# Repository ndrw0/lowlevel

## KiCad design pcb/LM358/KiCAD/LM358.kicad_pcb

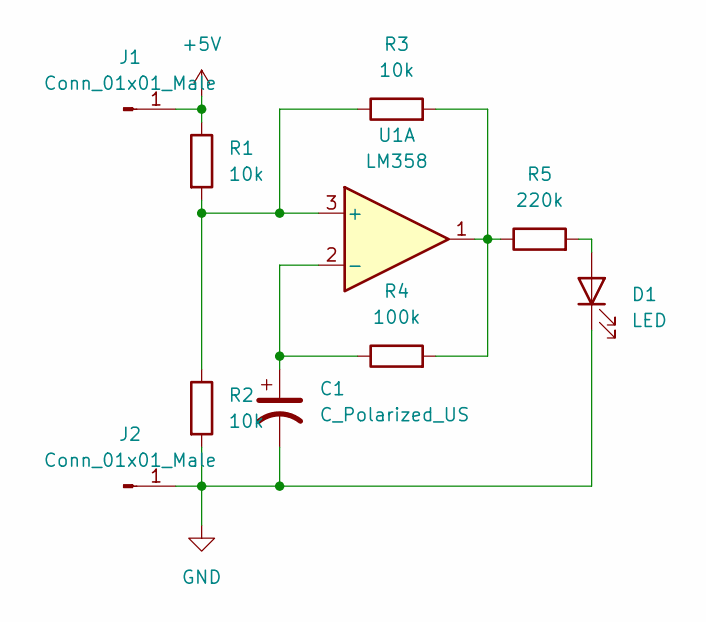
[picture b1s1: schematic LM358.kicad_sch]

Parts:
C1: C_Polarized_US
D1: LED
J1: Conn_01x01_Male
J2: Conn_01x01_Male; PinHeader_1x01_P2.54mm_Vertical
R1: 10k
R2, R3: 10k; R_Axial_DIN0204_L3.6mm_D1.6mm_P2.54mm_Vertical
R4: 100k; R_Axial_DIN0204_L3.6mm_D1.6mm_P2.54mm_Vertical
R5: 220k; R_Axial_DIN0204_L3.6mm_D1.6mm_P2.54mm_Vertical
U1: LM358

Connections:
+5V: J1.1, R1.1
GND: C1.2, D1.1 (K), J2.1, R2.2
unnamed: C1.1, R4.1, U1.2 (-)
unnamed: D1.2 (A), R5.2
unnamed: R1.2, R2.1, R3.1, U1.3 (+)
unnamed: R3.2, R4.2, R5.1, U1.1

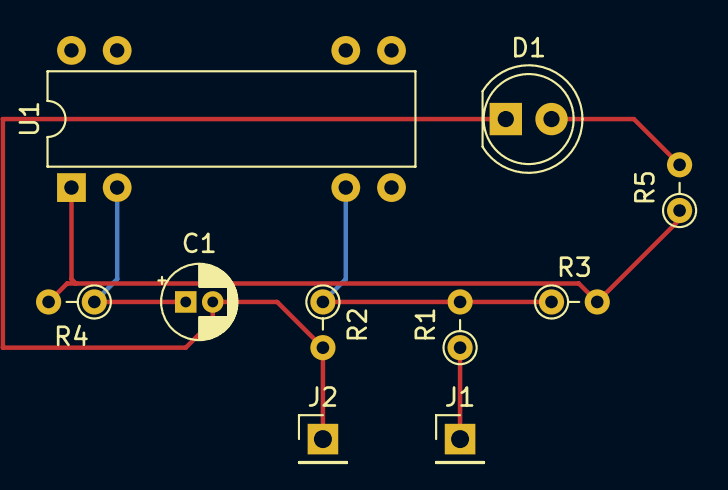
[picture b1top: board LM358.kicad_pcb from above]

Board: 2 copper layers, 10 parts (0 on the bottom side), 6 nets.

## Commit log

2022-08-10 20220810_2128
2022-08-20 add 'hwRNG'
2022-09-25 20220925
2023-01-04 20230104_161152
2023-01-10 20230110_131550
